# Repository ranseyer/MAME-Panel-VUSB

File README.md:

MAME-Panel-VUSB
===============

A Mame Controller with V-USB

Base Project: http://vusb.wikidot.com/project:mamepanel

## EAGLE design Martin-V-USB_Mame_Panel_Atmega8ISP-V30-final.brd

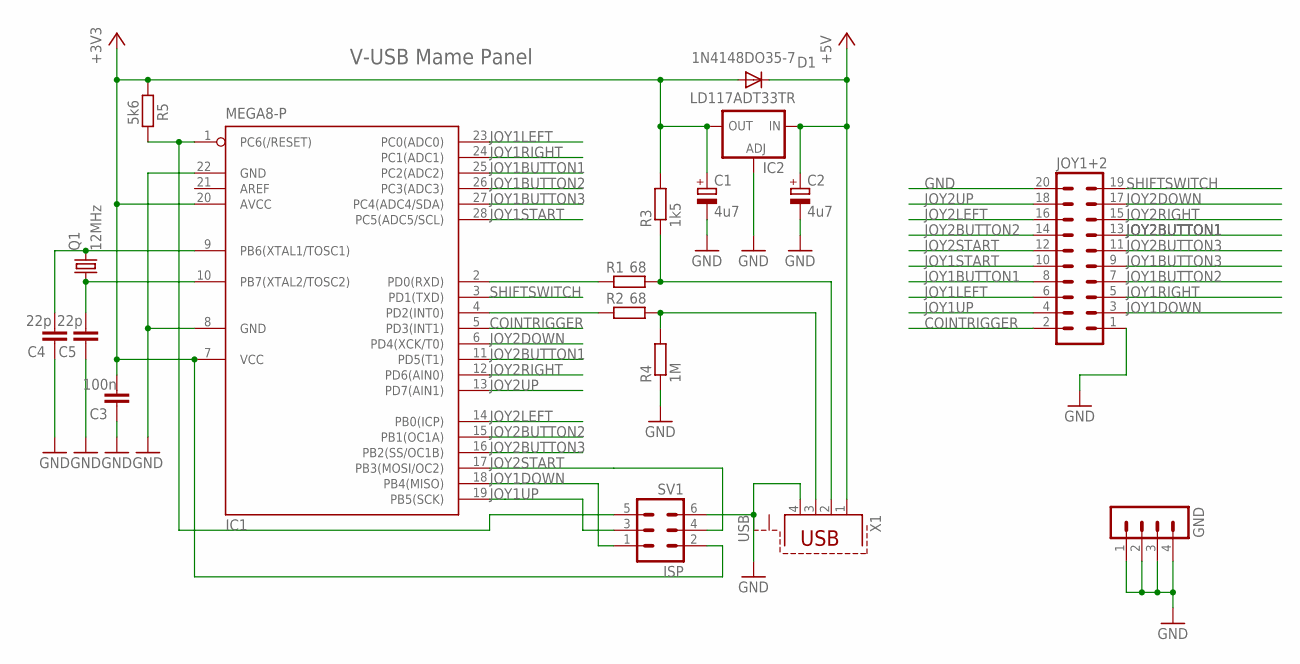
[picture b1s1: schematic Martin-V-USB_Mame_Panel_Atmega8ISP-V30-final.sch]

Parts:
C1, C2: 4u7; E2,5-5
C3: 100n; C050-030X075
C4, C5: 22p; C025-025X050
D1: 1N4148DO35-7; DO35-7
GND: MA04-1
IC1: MEGA8-P; DIL28-3
IC2: LD117ADT33TR; DPACK
JOY1+2: MA10-2
Q1: 12MHz; HC18U-V
R1, R2: 68; 0207/10
R3: 1k5; 0207/10
R4: 1M; 0207/10
R5: 5k6; 0207/10
SV1: ISP; ML6
X1: USB; PN61729-S

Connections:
+3V3: C1.+, C3.2, D1.A, IC1.7 (VCC), IC1.20 (AVCC), IC2.4 (OUT), R3.2, R5.1, SV1.2
+5V: C2.+, D1.C, IC2.3 (IN), X1.1
COINTRIGGER: IC1.5 (PD3(INT1)), JOY1+2.2
GND: C1.-, C2.-, C3.1, C4.1, C5.1, GND.1, GND.2, GND.3, GND.4, IC1.8 (GND), IC1.22 (GND), IC2.1 (ADJ), JOY1+2.1, JOY1+2.20, R4.1, SV1.6, X1.4
JOY1BUTTON1: IC1.25 (PC2(ADC2)), JOY1+2.8
JOY1BUTTON2: IC1.26 (PC3(ADC3)), JOY1+2.7
JOY1BUTTON3: IC1.27 (PC4(ADC4/SDA)), JOY1+2.9
JOY1DOWN: IC1.18 (PB4(MISO)), JOY1+2.3, SV1.1
JOY1LEFT: IC1.23 (PC0(ADC0)), JOY1+2.6
JOY1RIGHT: IC1.24 (PC1(ADC1)), JOY1+2.5
JOY1START: IC1.28 (PC5(ADC5/SCL)), JOY1+2.10
JOY1UP: IC1.19 (PB5(SCK)), JOY1+2.4, SV1.3
JOY2BUTTON1: IC1.11 (PD5(T1)), JOY1+2.13
JOY2BUTTON2: IC1.15 (PB1(OC1A)), JOY1+2.14
JOY2BUTTON3: IC1.16 (PB2(SS/OC1B)), JOY1+2.11
JOY2DOWN: IC1.6 (PD4(XCK/T0)), JOY1+2.17
JOY2LEFT: IC1.14 (PB0(ICP)), JOY1+2.16
JOY2RIGHT: IC1.12 (PD6(AIN0)), JOY1+2.15
JOY2START: IC1.17 (PB3(MOSI/OC2)), JOY1+2.12, SV1.4
JOY2UP: IC1.13 (PD7(AIN1)), JOY1+2.18
unnamed: IC1.2 (PD0(RXD)), R1.1
unnamed: IC1.4 (PD2(INT0)), R2.1
unnamed: IC1.1 (PC6(/RESET)), R5.2, SV1.5
unnamed: R1.2, R3.1, X1.2
unnamed: R2.2, R4.2, X1.3
unnamed: C4.2, IC1.9 (PB6(XTAL1/TOSC1)), Q1.2
unnamed: C5.2, IC1.10 (PB7(XTAL2/TOSC2)), Q1.1
SHIFTSWITCH: IC1.3 (PD1(TXD)), JOY1+2.19

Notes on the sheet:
V-USB Mame Panel

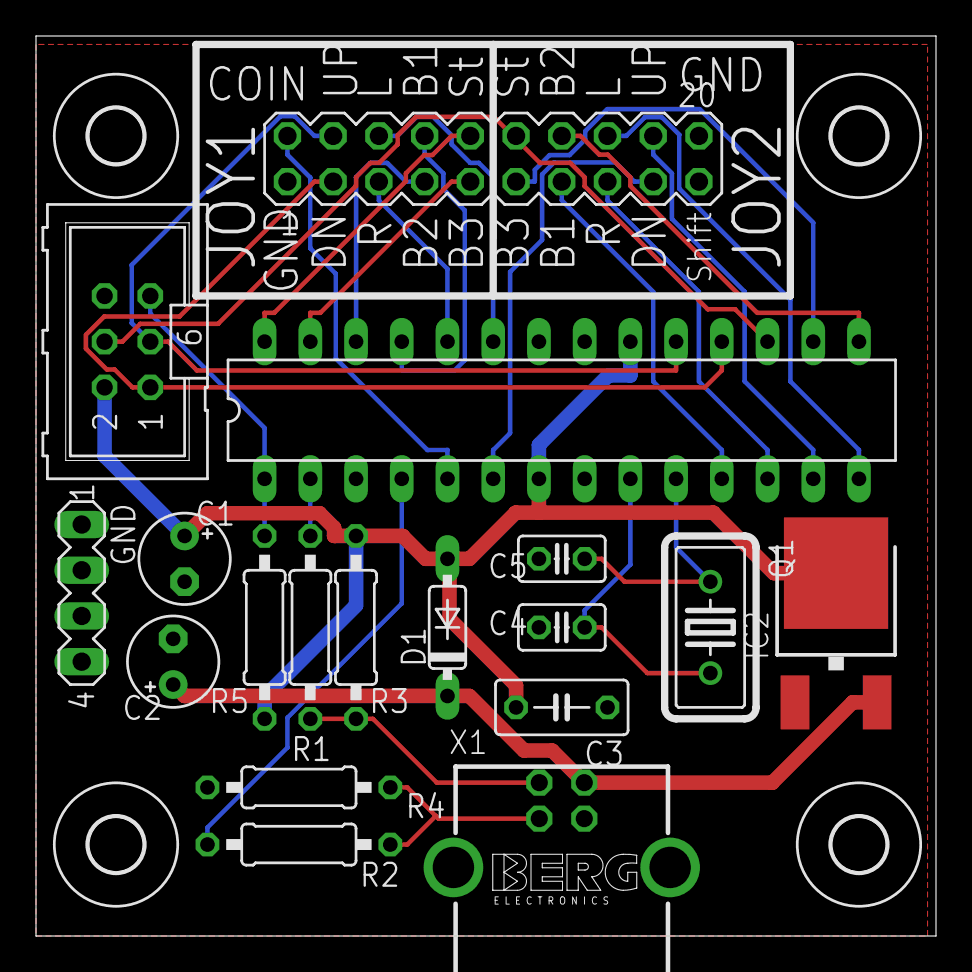
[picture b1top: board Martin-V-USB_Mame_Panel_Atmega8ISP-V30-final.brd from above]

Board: 2 copper layers, 50.0 x 50.0 mm, 22 parts (0 on the bottom side), 28 nets.

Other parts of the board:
U$1, U$2, U$3, U$4: 3,0

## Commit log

2013-03-17 Initial Upload
2014-02-09 Pictures
2014-02-09 Picture
2014-09-18 New Board Revision
2014-09-18 Board Routed
2016-03-07 Leonardo Version
2016-03-30 double click
